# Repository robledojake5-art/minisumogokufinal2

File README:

PROYECTO "ROBOT MINISUMO GOKU"

Este proyecto del robot minisumo esta pensado para que luche contra otros minisumos en un area circular y mas especificame
los tire fuera del area de combate

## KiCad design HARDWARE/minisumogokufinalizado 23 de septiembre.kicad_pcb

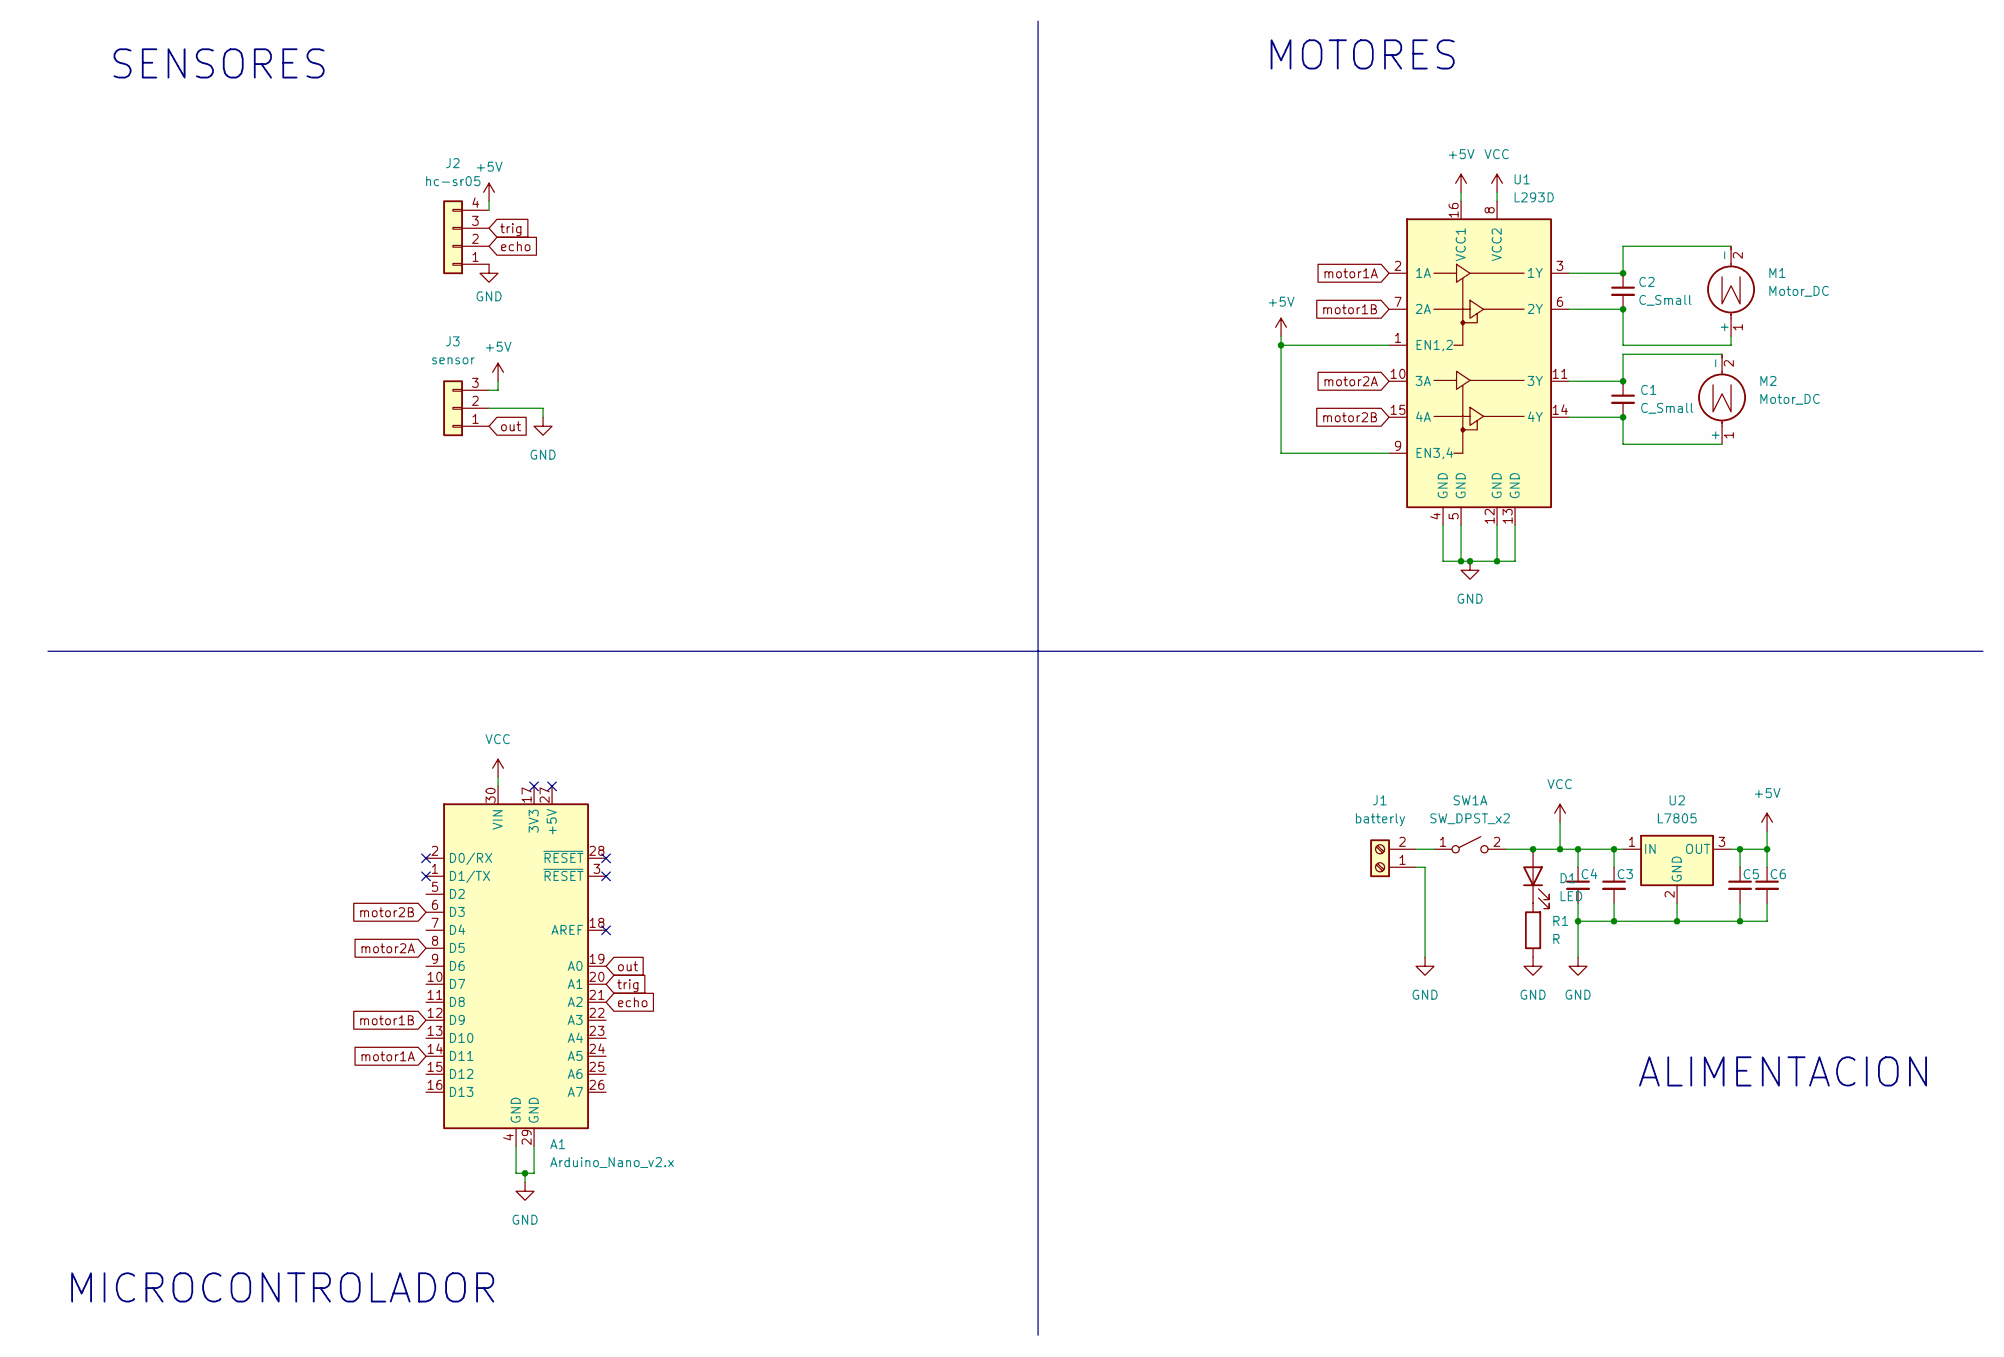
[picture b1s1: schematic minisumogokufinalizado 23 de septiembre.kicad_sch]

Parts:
A1: Arduino_Nano_v2.x; arduino_nano_header
C1, C2: C_Small; CAP_0.2
C3, C4, C5, C6: C_Small; CAP_0.1
D1: LED; LED_D5.0mm
J1: batterly; TerminalBlock_Phoenix_MKDS-1,5-2_1x02_P5.00mm_Horizontal
J2: hc-sr05; pin_strip_4
J3: sensor; Pin_Header_3
M1, M2: Motor_DC; BORNERA2_AZUL
R1: R; RES0.3
SW1: SW_DPST_x2; PinHeader_1x03_P2.54mm_Vertical
U1: L293D; DIP880W50P254L2000H510Q16
U2: L7805; TO-220-2

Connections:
+5V: C5.1, C6.1, J2.4, J3.3, U1.1 (EN1,2), U1.9 (EN3,4), U1.16 (VCC1), U2.3 (OUT)
GND: A1.4 (GND), A1.29 (GND), C3.2, C4.2, C5.2, C6.2, J1.1, J2.1, J3.2, R1.1, U1.4 (GND), U1.5 (GND), U1.12 (GND), U1.13 (GND), U2.2 (GND)
unnamed: D1.1 (K), R1.2
unnamed: J1.2, SW1.1 (A)
unnamed: C2.2, M1.1 (+), U1.6 (2Y)
unnamed: C2.1, M1.2 (-), U1.3 (1Y)
unnamed: C1.2, M2.1 (+), U1.14 (4Y)
unnamed: C1.1, M2.2 (-), U1.11 (3Y)
VCC: A1.30 (VIN), C3.1, C4.1, D1.2 (A), SW1.2 (B), U1.8 (VCC2), U2.1 (IN)
echo: A1.21 (A2), J2.2
motor1A: A1.14 (D11), U1.2 (1A)
motor1B: A1.12 (D9), U1.7 (2A)
motor2A: A1.8 (D5), U1.10 (3A)
motor2B: A1.6 (D3), U1.15 (4A)
out: A1.19 (A0), J3.1
trig: A1.20 (A1), J2.3

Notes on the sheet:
ALIMENTACION
MICROCONTROLADOR
MOTORES
SENSORES

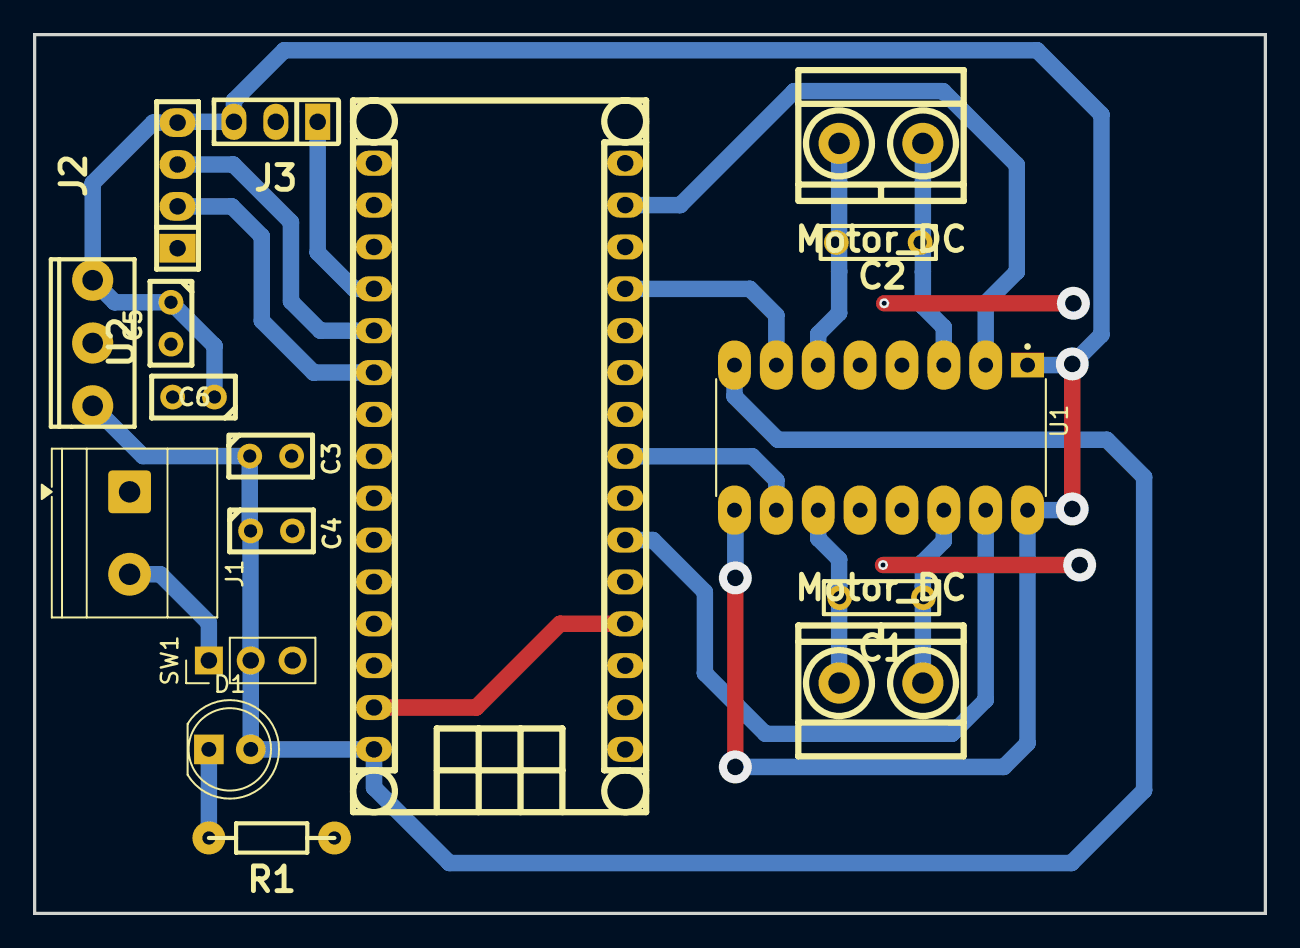
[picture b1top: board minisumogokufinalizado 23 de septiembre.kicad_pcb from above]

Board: 2 copper layers, 74.7 x 53.3 mm, 17 parts (0 on the bottom side), 16 nets.
